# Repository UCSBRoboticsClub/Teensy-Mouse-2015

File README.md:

# Teensy-Mouse-2015
Micromoue but even smaller. Using a Teensy and vl6180 sensors

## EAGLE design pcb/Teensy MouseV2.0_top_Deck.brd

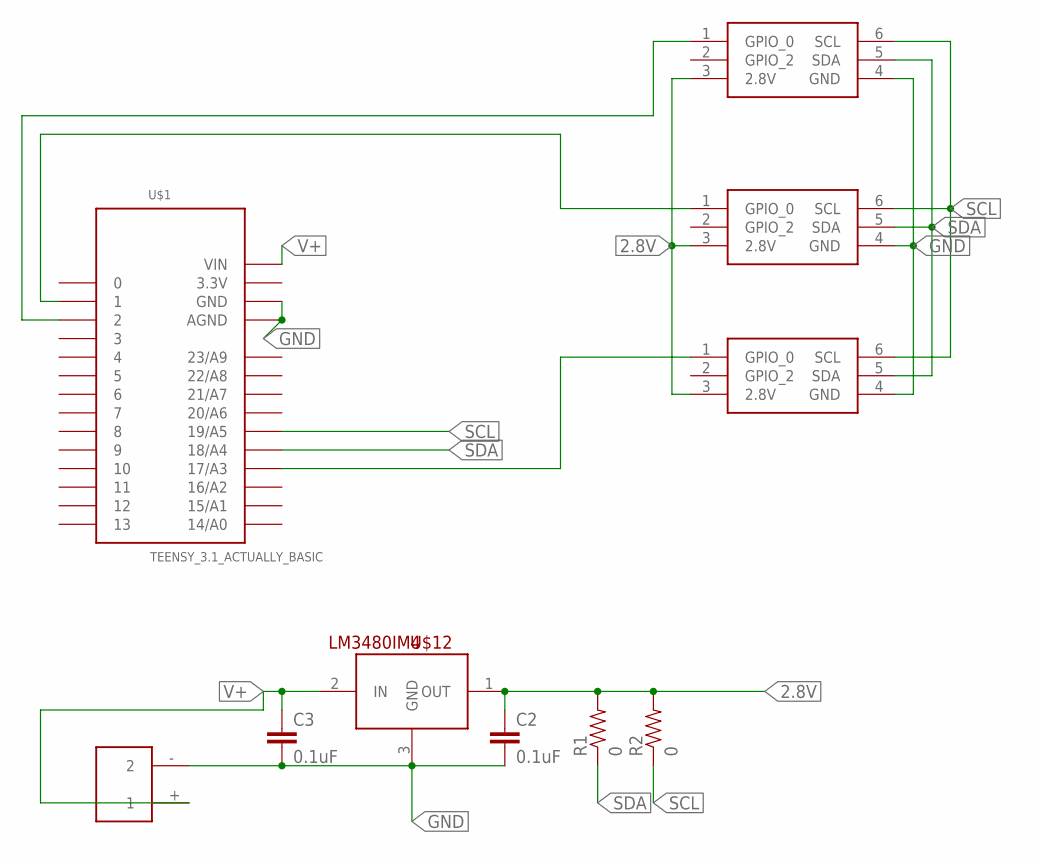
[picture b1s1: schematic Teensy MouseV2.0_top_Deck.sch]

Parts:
C2, C3: 0.1uF; 0603-CAP
R1, R2: 0; 0603
U$1: TEENSY_3.1_ACTUALLY_BASIC; TEENSY_3.0_ACTUALLY_BASIC
U$2: PICOBLADE2X
U$9, U$10, U$11: PATRICK'S_ST_SENSOR_BOARD; 2X3HEADER
U$12: LM3480IM4; SOT23-3

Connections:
2.8V: C2.1, R1.2, R2.2, U$9.3 (2.8V), U$10.3 (2.8V), U$11.3 (2.8V), U$12.1 (OUT)
3.3V: U$1.3.3V
GND: C2.2, C3.2, U$1.AGND, U$1.GND, U$2.- (2), U$9.4 (GND), U$10.4 (GND), U$11.4 (GND), U$12.3 (GND)
unnamed: U$1.17/A3, U$11.1 (GPIO_0)
unnamed: U$1.1, U$10.1 (GPIO_0)
unnamed: U$1.2, U$9.1 (GPIO_0)
SCL: R2.1, U$1.19/A5, U$9.6 (SCL), U$10.6 (SCL), U$11.6 (SCL)
SDA: R1.1, U$1.18/A4, U$9.5 (SDA), U$10.5 (SDA), U$11.5 (SDA)
V+: C3.1, U$1.VIN, U$2.+ (1), U$12.2 (IN)

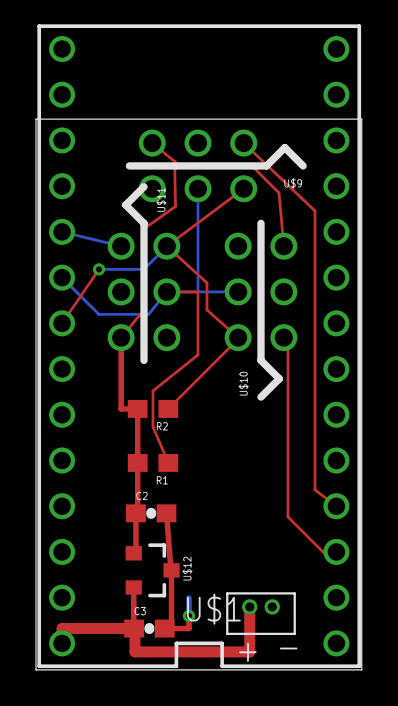
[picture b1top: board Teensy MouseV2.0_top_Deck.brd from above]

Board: 2 copper layers, 18.1 x 30.6 mm, 10 parts (0 on the bottom side), 8 nets.

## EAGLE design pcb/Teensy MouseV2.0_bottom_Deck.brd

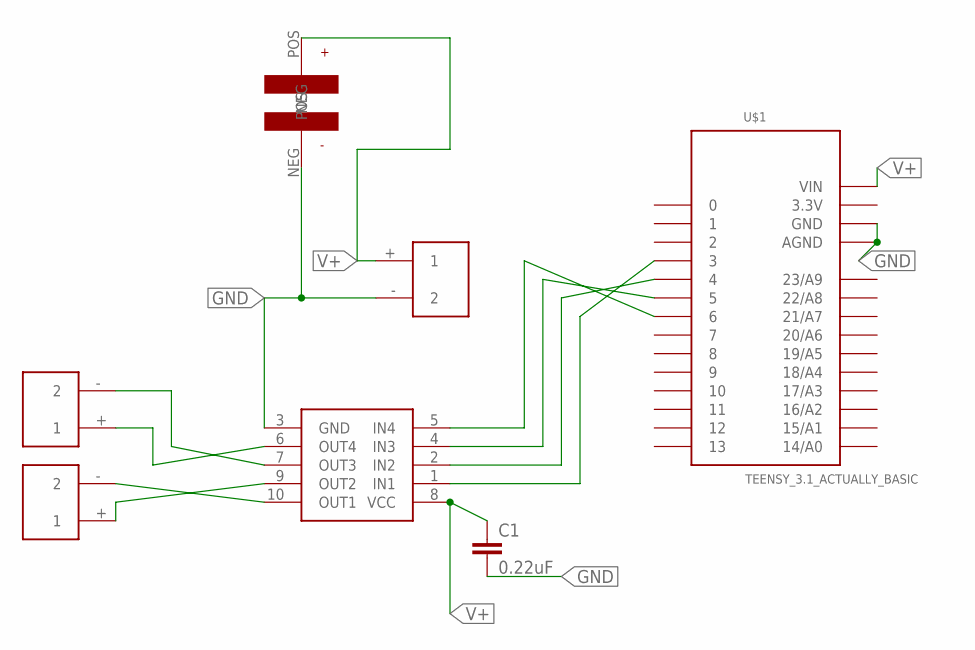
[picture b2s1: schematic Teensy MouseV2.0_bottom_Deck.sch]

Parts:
C1: 0.22uF; 0603-CAP
U$1: TEENSY_3.1_ACTUALLY_BASIC; TEENSY_3.0_ACTUALLY_BASIC
U$2, U$3: TEENSYMOUSEMOTORS; TEENSYMOUSEMOTRS
U$4: PICOBLADE2X
U$5: 47UFBUTTONCAP; ALUMINIUMELECTOCAP
U$7: A3901DUALHBRIDGE; 10WFDFN

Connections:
3.3V: U$1.3.3V
GND: C1.2, U$1.AGND, U$1.GND, U$4.- (2), U$5.NEG, U$7.3 (GND)
unnamed: U$3.- (2), U$7.7 (OUT3)
unnamed: U$3.+ (1), U$7.6 (OUT4)
unnamed: U$2.- (2), U$7.10 (OUT1)
unnamed: U$2.+ (1), U$7.9 (OUT2)
unnamed: U$1.6, U$7.5 (IN4)
unnamed: U$1.5, U$7.4 (IN3)
unnamed: U$1.4, U$7.2 (IN2)
unnamed: U$1.3, U$7.1 (IN1)
V+: C1.1, U$1.VIN, U$4.+ (1), U$5.POS, U$7.8 (VCC)

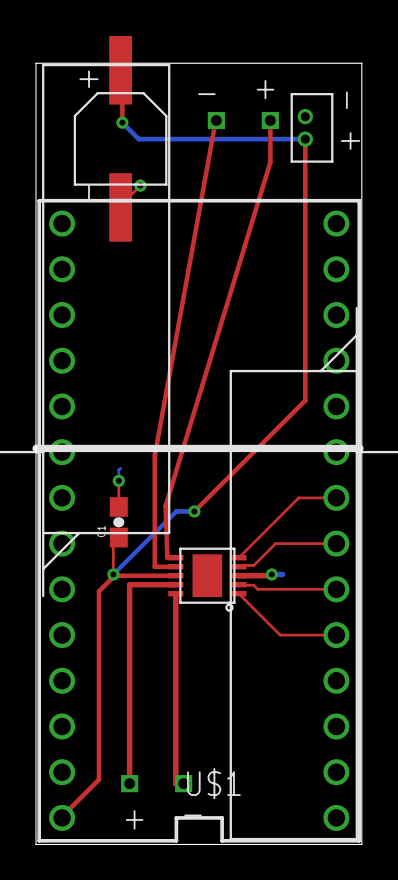
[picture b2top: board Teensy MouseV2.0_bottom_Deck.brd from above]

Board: 2 copper layers, 18.1 x 43.4 mm, 7 parts (0 on the bottom side), 10 nets.

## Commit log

2015-04-07 Added pcb designs
2015-04-11 Added wheel bit for the Teensy Mouse
    Printing 2 would be good
2015-04-18 Changed chamfer angle
2015-05-15 Changed globals
2015-05-16 Removed unnecessary things
2015-05-16 Some of Adam's stuff
2015-05-16 Compiles
    lololololololololololololol
2015-05-16 yolo forward swag
    fer jesus
2015-05-17 New forward code
2015-05-17 Adam did it
2015-05-17 Fixed nick's thing
2015-05-17 just changed drivetime
2015-05-17 more tuning
2015-05-17 pretty good
2015-05-17 Better edge ignore

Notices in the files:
parts and their libraries:
SparkFun-Capacitors: Licensing: Creative Commons ShareAlike 4.0 International - https://creativecommons.org/licenses/by-sa/4.0
